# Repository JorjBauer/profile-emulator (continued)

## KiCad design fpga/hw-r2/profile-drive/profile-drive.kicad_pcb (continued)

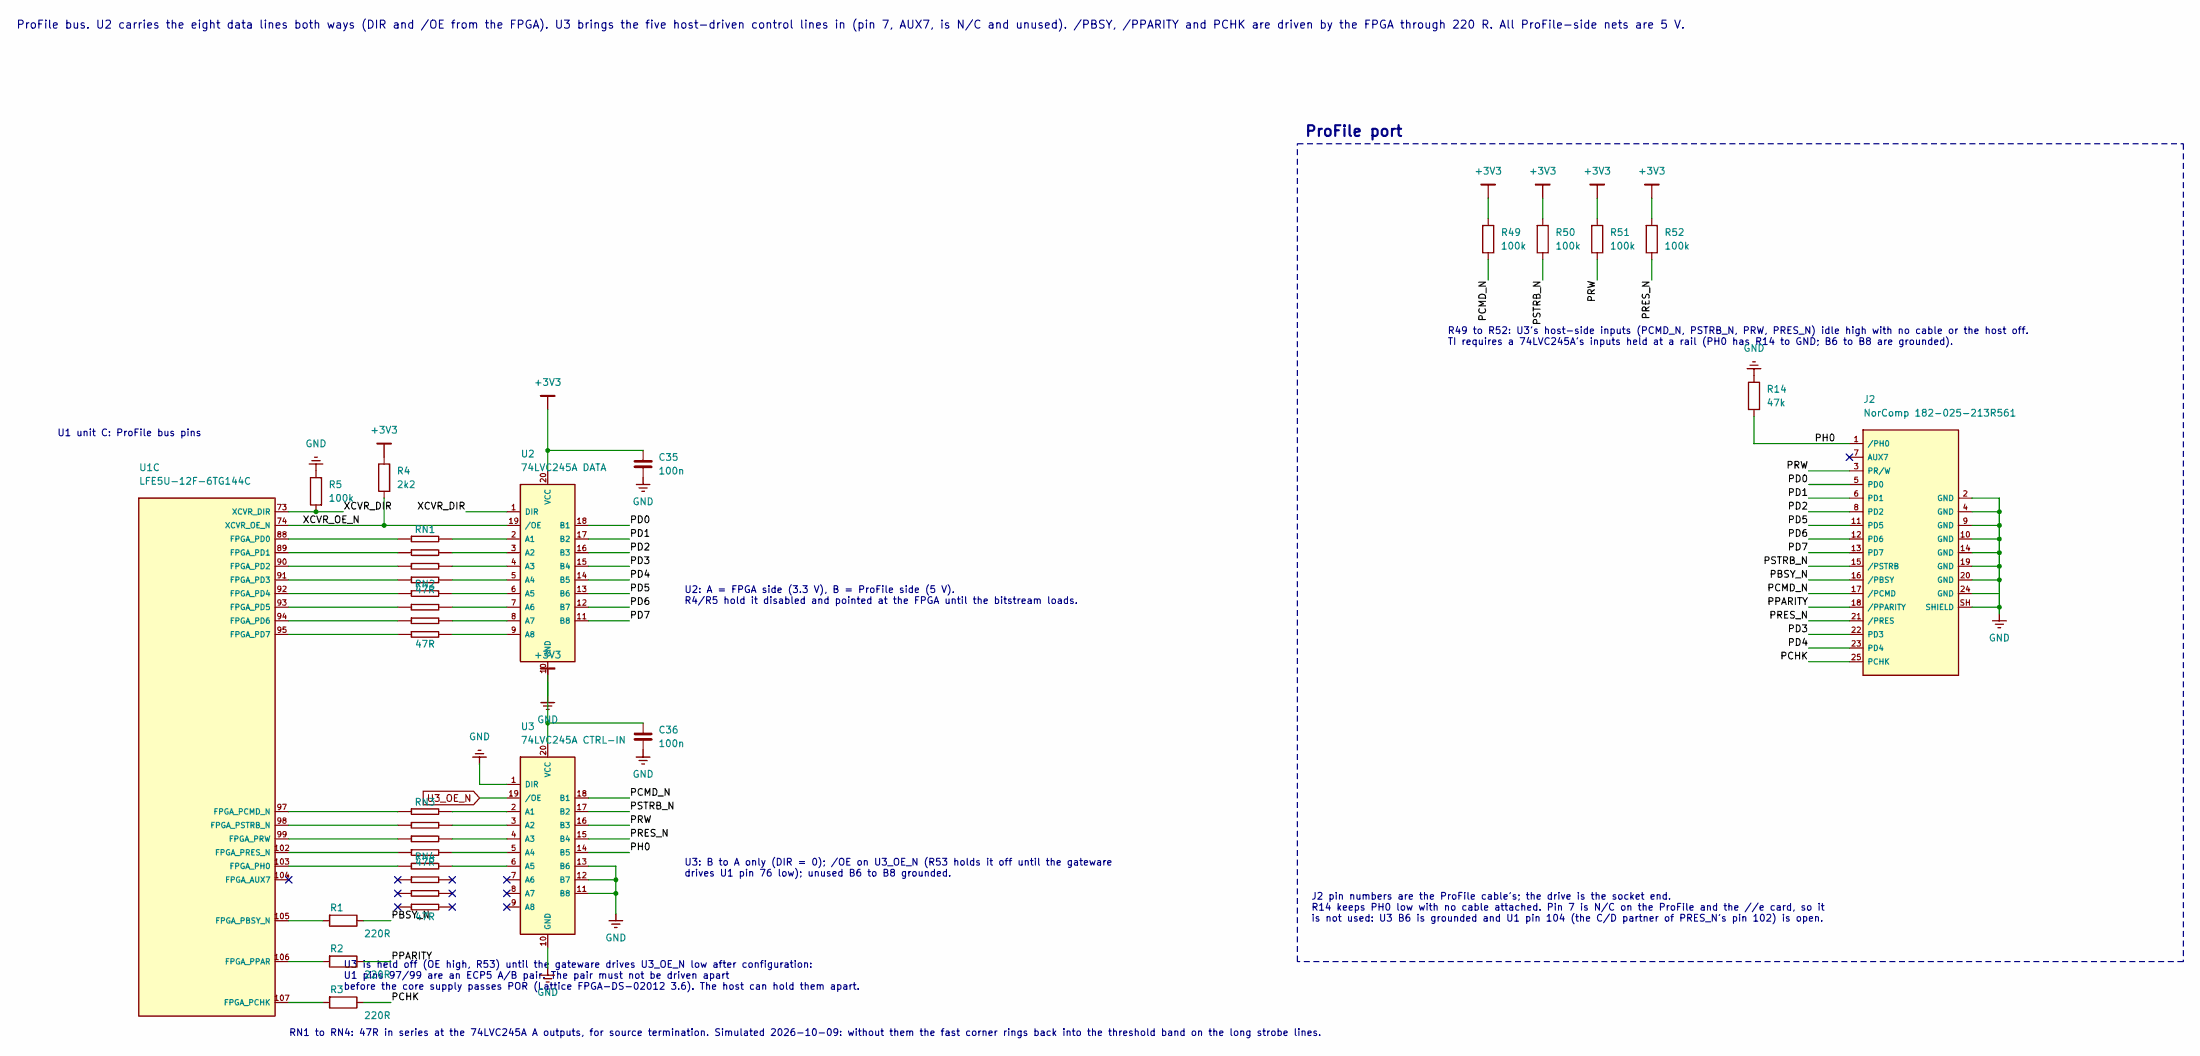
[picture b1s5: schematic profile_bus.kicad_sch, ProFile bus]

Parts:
C35, C36: 100n; C_0603_1608Metric; MPN Samsung CL10B104KO8NNNC; LCSC C66501
J2: NorComp 182-025-213R561; DSUB-25_Female_Horizontal_NorComp_182-025-213R561; MPN NorComp 182-025-213R561; LCSC C17257261
R1, R2, R3: 220R; R_0603_1608Metric; MPN Yageo RC0603FR-07220RL; LCSC C107696
R4: 2k2; R_0603_1608Metric; MPN Yageo RC0603FR-072K2L; LCSC C114662
R5, R49, R50, R51, R52: 100k; R_0603_1608Metric; MPN Yageo RC0603FR-07100KL; LCSC C14675
R14: 47k; R_0603_1608Metric; MPN Yageo RC0603FR-0747KL; LCSC C105579
RN1, RN2, RN3, RN4: 47R; R_Array_Convex_4x0603_Yageo_YC164; MPN Yageo YC164-FR-0747RL; LCSC C606217
U1: LFE5U-12F-6TG144C; TQFP-144_20x20mm_P0.5mm; MPN Lattice LFE5U-12F-6TG144C; LCSC C19979181
U2: 74LVC245A DATA; TSSOP-20_4.4x6.5mm_P0.65mm; MPN TI SN74LVC245APWR; LCSC C7848
U3: 74LVC245A CTRL-IN; TSSOP-20_4.4x6.5mm_P0.65mm; MPN TI SN74LVC245APWR; LCSC C7848

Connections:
/ProFile bus/PBSY_N: J2.16 (/PBSY), R1.2
/ProFile bus/PCHK: J2.25 (PCHK), R3.2
/ProFile bus/PCMD_N: J2.17 (/PCMD), R49.2, U3.18 (B1)
/ProFile bus/PD0: J2.5 (PD0), U2.18 (B1)
/ProFile bus/PD1: J2.6 (PD1), U2.17 (B2)
/ProFile bus/PD2: J2.8 (PD2), U2.16 (B3)
/ProFile bus/PD3: J2.22 (PD3), U2.15 (B4)
/ProFile bus/PD4: J2.23 (PD4), U2.14 (B5)
/ProFile bus/PD5: J2.11 (PD5), U2.13 (B6)
/ProFile bus/PD6: J2.12 (PD6), U2.12 (B7)
/ProFile bus/PD7: J2.13 (PD7), U2.11 (B8)
/ProFile bus/PH0: J2.1 (/PH0), R14.1, U3.14 (B5)
/ProFile bus/PPARITY: J2.18 (/PPARITY), R2.2
/ProFile bus/PRES_N: J2.21 (/PRES), R52.2, U3.15 (B4)
/ProFile bus/PRW: J2.3 (PR/W), R51.2, U3.16 (B3)
/ProFile bus/PSTRB_N: J2.15 (/PSTRB), R50.2, U3.17 (B2)
/ProFile bus/XCVR_DIR: R5.1, U1.73 (XCVR_DIR), U2.1 (DIR)
/ProFile bus/XCVR_OE_N: R4.1, U1.74 (XCVR_OE_N), U2.19 (/OE)
unnamed: R1.1, U1.105 (FPGA_PBSY_N)
unnamed: R3.1, U1.107 (FPGA_PCHK)
unnamed: RN3.1, U1.97 (FPGA_PCMD_N)
unnamed: RN1.1, U1.88 (FPGA_PD0)
unnamed: RN1.2, U1.89 (FPGA_PD1)
unnamed: RN1.3, U1.90 (FPGA_PD2)
unnamed: RN1.4, U1.91 (FPGA_PD3)
unnamed: RN2.1, U1.92 (FPGA_PD4)
unnamed: RN2.2, U1.93 (FPGA_PD5)
unnamed: RN2.3, U1.94 (FPGA_PD6)
unnamed: RN2.4, U1.95 (FPGA_PD7)
unnamed: RN4.1, U1.103 (FPGA_PH0)
unnamed: R2.1, U1.106 (FPGA_PPAR)
unnamed: RN3.4, U1.102 (FPGA_PRES_N)
unnamed: RN3.3, U1.99 (FPGA_PRW)
unnamed: RN3.2, U1.98 (FPGA_PSTRB_N)
unnamed: RN1.8, U2.2 (A1)
unnamed: RN1.7, U2.3 (A2)
unnamed: RN1.6, U2.4 (A3)
unnamed: RN1.5, U2.5 (A4)
unnamed: RN2.8, U2.6 (A5)
unnamed: RN2.7, U2.7 (A6)
unnamed: RN2.6, U2.8 (A7)
unnamed: RN2.5, U2.9 (A8)
unnamed: RN3.8, U3.2 (A1)
unnamed: RN3.7, U3.3 (A2)
unnamed: RN3.6, U3.4 (A3)
unnamed: RN3.5, U3.5 (A4)
unnamed: RN4.8, U3.6 (A5)
U3_OE_N: U3.19 (/OE); also elsewhere on the board

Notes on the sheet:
ProFile bus. U2 carries the eight data lines both ways (DIR and /OE from the FPGA). U3 brings the five host-driven control lines in (pin 7, AUX7, is N/C and unused). /PBSY, /PPARITY and PCHK are driven by the FPGA through 220 R. All ProFile-side nets are 5 V.
U1 unit C: ProFile bus pins
U2: A = FPGA side (3.3 V), B = ProFile side (5 V). R4/R5 hold it disabled and pointed at the FPGA until the bitstream loads.
U3: B to A only (DIR = 0); /OE on U3_OE_N (R53 holds it off until the gateware drives U1 pin 76 low); unused B6 to B8 grounded.
ProFile port
J2 pin numbers are the ProFile cable's; the drive is the socket end. R14 keeps PH0 low with no cable attached. Pin 7 is N/C on the ProFile and the //e card, so it is not used: U3 B6 is grounded and U1 pin 104 (the C/D partner of PRES_N's pin 102) is open.
RN1 to RN4: 47R in series at the 74LVC245A A outputs, for source termination. Simulated 2026-10-09: without them the fast corner rings back into the threshold band on the long strobe lines.
R49 to R52: U3's host-side inputs (PCMD_N, PSTRB_N, PRW, PRES_N) idle high with no cable or the host off. TI requires a 74LVC245A's inputs held at a rail (PH0 has R14 to GND; B6 to B8 are grounded).
U3 is held off (OE high, R53) until the gateware drives U3_OE_N low after configuration: U1 pins 97/99 are an ECP5 A/B pair. The pair must not be driven apart before the core supply passes POR (Lattice FPGA-DS-02012 3.6). The host can hold them apart.

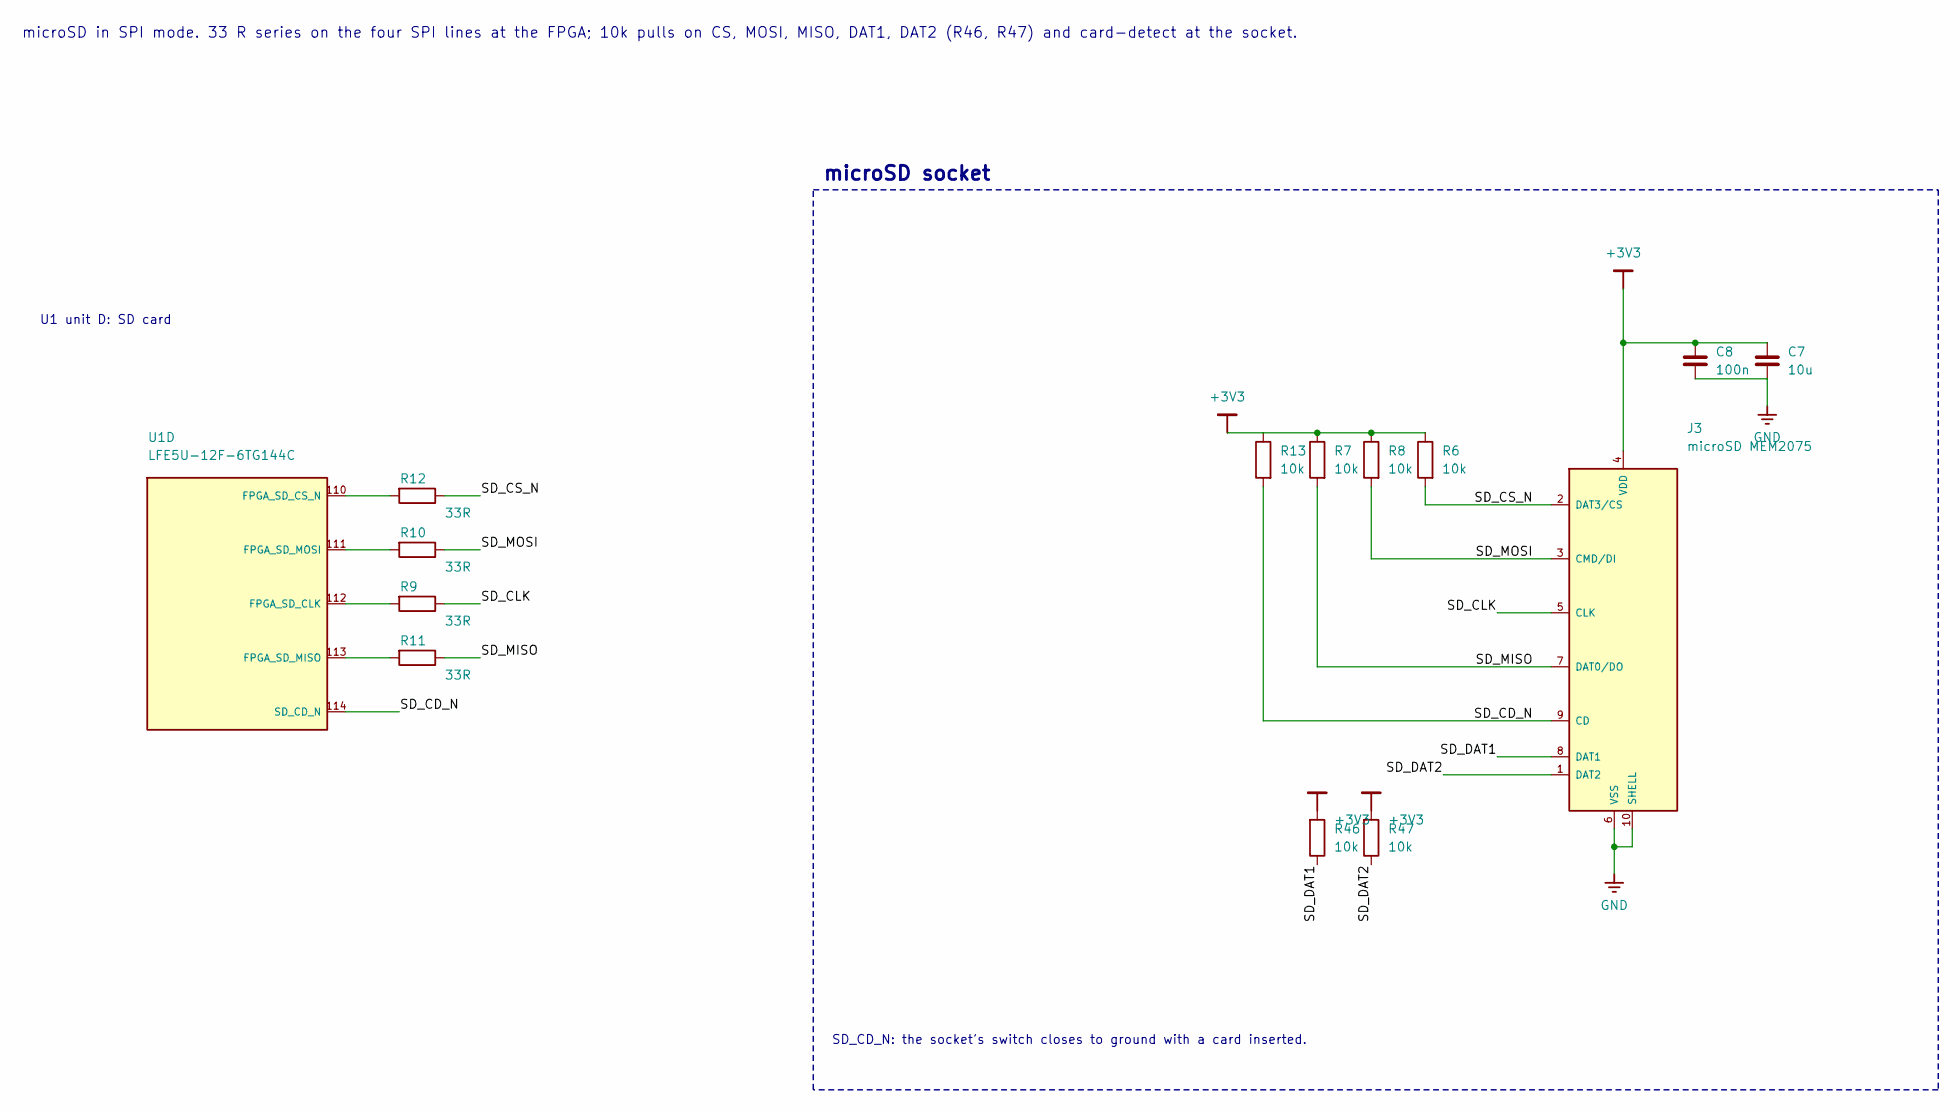
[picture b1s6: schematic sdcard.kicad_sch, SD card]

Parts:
C7: 10u; C_0603_1608Metric; MPN Murata GRM188R61E106MA73D; LCSC C91606
C8: 100n; C_0603_1608Metric; MPN Samsung CL10B104KO8NNNC; LCSC C66501
J3: microSD MEM2075; microSD_GCT_MEM2075; MPN GCT MEM2075-00-140-01-A; LCSC C3029735
R6, R7, R8, R13, R46, R47: 10k; R_0603_1608Metric; MPN Yageo RC0603FR-0710KL; LCSC C98220
R9, R10, R11, R12: 33R; R_0603_1608Metric; MPN Yageo RC0603FR-0733RL; LCSC C108661
U1: LFE5U-12F-6TG144C; TQFP-144_20x20mm_P0.5mm; MPN Lattice LFE5U-12F-6TG144C; LCSC C19979181

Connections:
/SD card/SD_CD_N: J3.9 (CD), R13.1, U1.114 (SD_CD_N)
/SD card/SD_CLK: J3.5 (CLK), R9.2
/SD card/SD_CS_N: J3.2 (DAT3/CS), R6.1, R12.2
/SD card/SD_DAT1: J3.8 (DAT1), R46.2
/SD card/SD_DAT2: J3.1 (DAT2), R47.2
/SD card/SD_MISO: J3.7 (DAT0/DO), R7.1, R11.2
/SD card/SD_MOSI: J3.3 (CMD/DI), R8.1, R10.2
unnamed: R9.1, U1.112 (FPGA_SD_CLK)
unnamed: R12.1, U1.110 (FPGA_SD_CS_N)
unnamed: R11.1, U1.113 (FPGA_SD_MISO)
unnamed: R10.1, U1.111 (FPGA_SD_MOSI)

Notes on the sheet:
microSD in SPI mode. 33 R series on the four SPI lines at the FPGA; 10k pulls on CS, MOSI, MISO, DAT1, DAT2 (R46, R47) and card-detect at the socket.
U1 unit D: SD card
microSD socket
SD_CD_N: the socket's switch closes to ground with a card inserted.

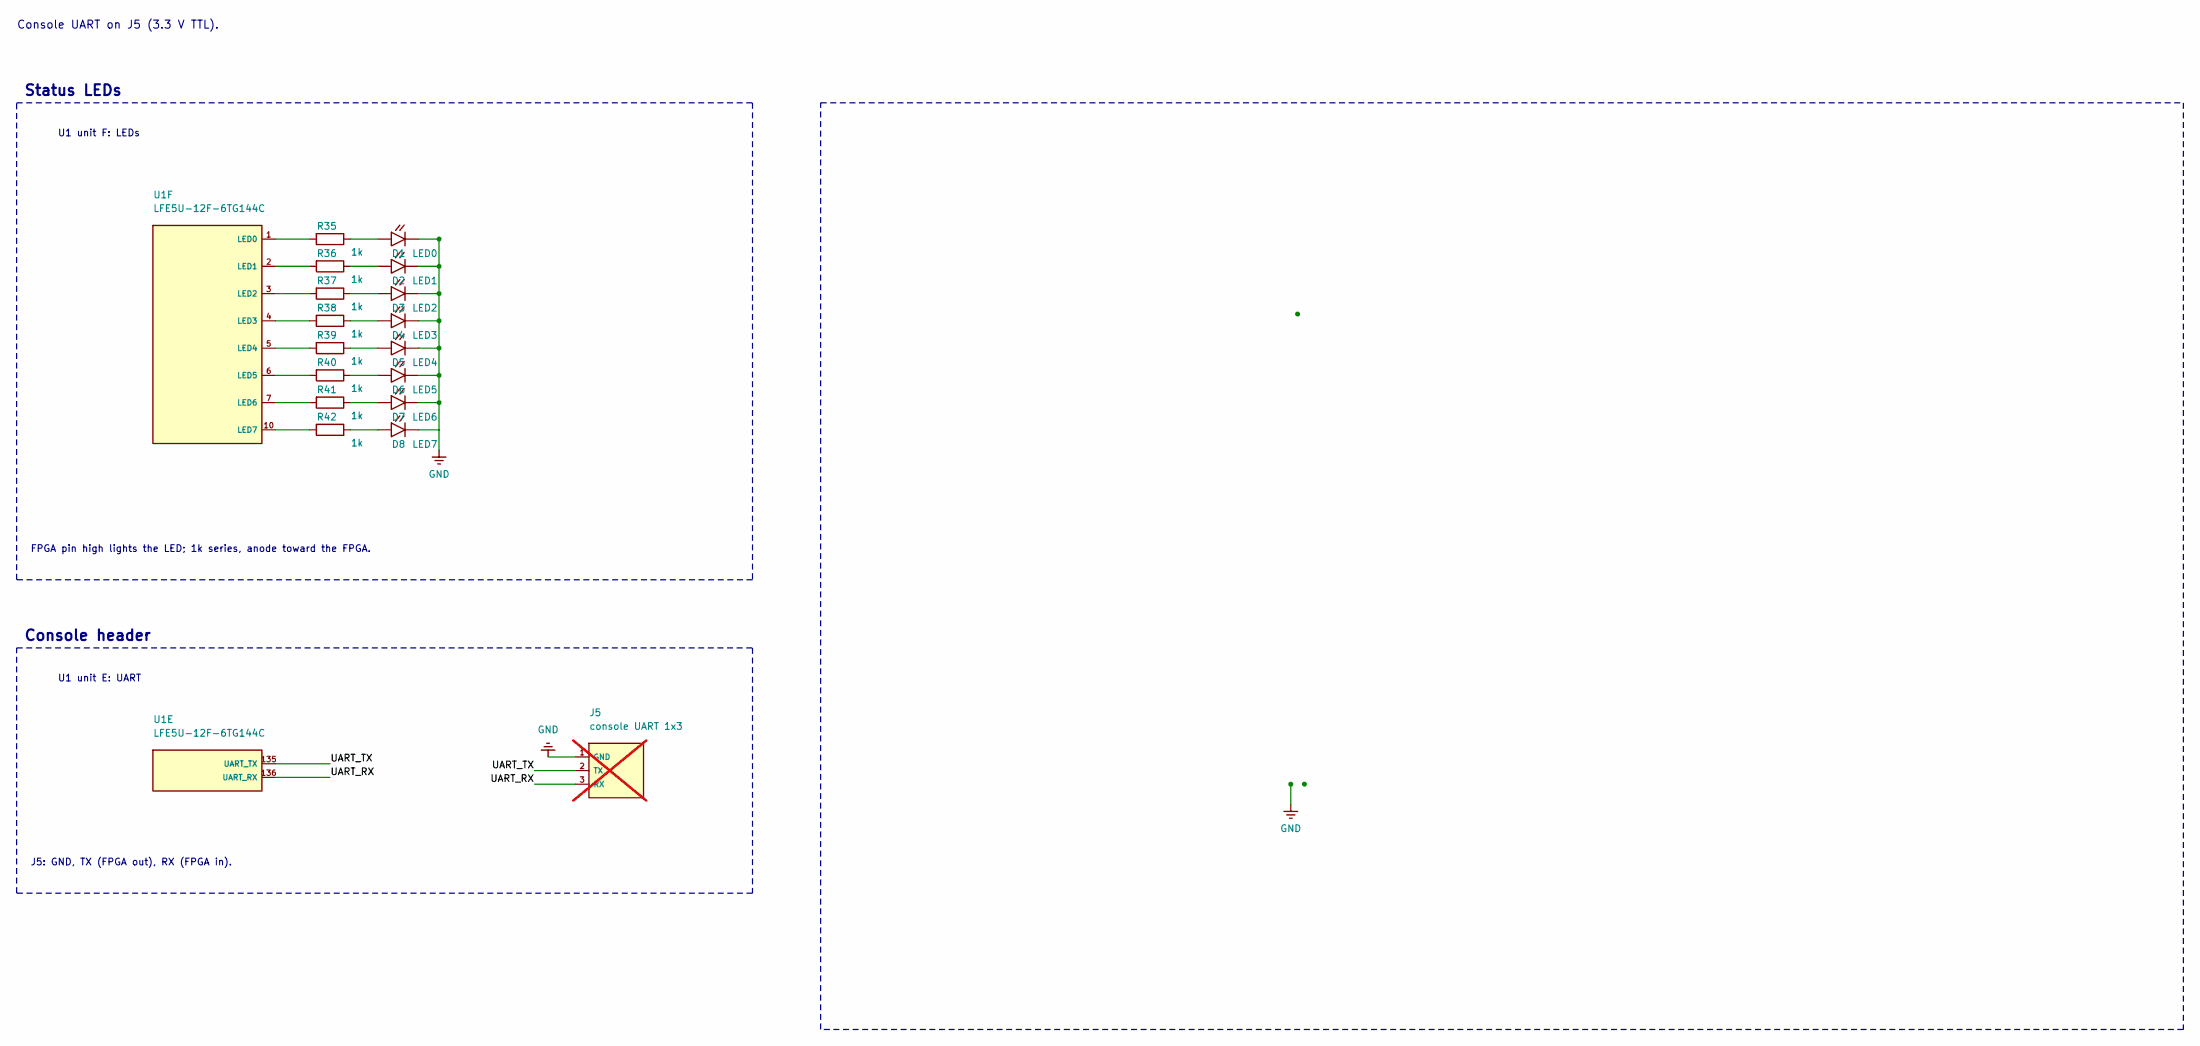
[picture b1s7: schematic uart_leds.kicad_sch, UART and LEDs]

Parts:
D1: LED0; LED_0603_1608Metric; LCSC C2286
D2: LED1; LED_0603_1608Metric; LCSC C2286
D3: LED2; LED_0603_1608Metric; LCSC C2286
D4: LED3; LED_0603_1608Metric; LCSC C2286
D5: LED4; LED_0603_1608Metric; LCSC C2286
D6: LED5; LED_0603_1608Metric; LCSC C2286
D7: LED6; LED_0603_1608Metric; LCSC C2286
D8: LED7; LED_0603_1608Metric; LCSC C2286
J5: console UART 1x3; PinHeader_1x03_P2.54mm_Vertical; not fitted
R35, R36, R37, R38, R39, R40, R41, R42: 1k; R_0603_1608Metric; MPN Yageo RC0603FR-071KL; LCSC C22548
U1: LFE5U-12F-6TG144C; TQFP-144_20x20mm_P0.5mm; MPN Lattice LFE5U-12F-6TG144C; LCSC C19979181

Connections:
/UART and LEDs/UART_RX: J5.3 (RX), U1.136 (UART_RX)
/UART and LEDs/UART_TX: J5.2 (TX), U1.135 (UART_TX)
unnamed: D1.2 (A), R35.2
unnamed: D2.2 (A), R36.2
unnamed: D3.2 (A), R37.2
unnamed: D4.2 (A), R38.2
unnamed: D5.2 (A), R39.2
unnamed: D6.2 (A), R40.2
unnamed: D7.2 (A), R41.2
unnamed: D8.2 (A), R42.2
unnamed: R35.1, U1.1 (LED0)
unnamed: R36.1, U1.2 (LED1)
unnamed: R37.1, U1.3 (LED2)
unnamed: R38.1, U1.4 (LED3)
unnamed: R39.1, U1.5 (LED4)
unnamed: R40.1, U1.6 (LED5)
unnamed: R41.1, U1.7 (LED6)
unnamed: R42.1, U1.10 (LED7)

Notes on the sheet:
Console UART on J5 (3.3 V TTL).
Status LEDs
U1 unit F: LEDs
FPGA pin high lights the LED; 1k series, anode toward the FPGA.
Console header
U1 unit E: UART
J5: GND, TX (FPGA out), RX (FPGA in).

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
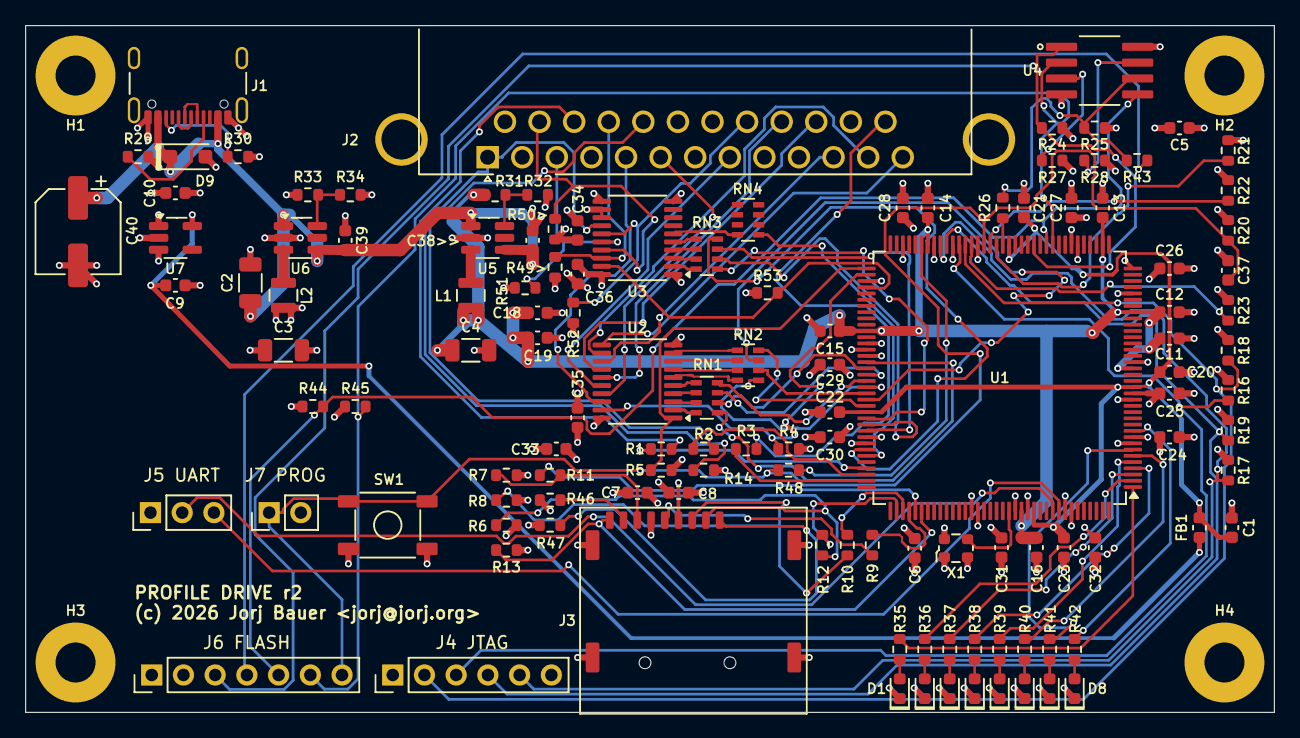
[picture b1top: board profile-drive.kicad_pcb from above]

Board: 4 copper layers, 100.0 x 55.0 mm, 127 parts (0 on the bottom side), 109 nets.

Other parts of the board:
H1, H2, H3, H4: M3; MountingHole_3.2mm_M3_Pad

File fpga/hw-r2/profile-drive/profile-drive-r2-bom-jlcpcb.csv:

"Comment","Designator","Footprint","Manufacturer Part","LCSC Part #"
"10u","C1,C7,C9,C18,C19,C33,C34,C38,C39","C_0603_1608Metric","Murata GRM188R61E106MA73D","C91606"
"22u","C2,C3,C4","C_1206_3216Metric","Samsung CL31A226KAHNNNE","C12891"
"100n","C5,C6,C8,C11,C12,C13,C14,C15,C16,C20,C21,C22,C23,C24,C25,C26,C27,C28,C29,C30,C31,C32,C35,C36","C_0603_1608Metric","Samsung CL10B104KO8NNNC","C66501"
"1u","C10,C37","C_0603_1608Metric","Samsung CL10B105KA8NNNC","C29936"
"100u","C40","CP_Elec_6.3x5.8","Panasonic EEE-FK1C101P","C128532"
"LED red 0603","D1,D2,D3,D4,D5,D6,D7,D8","LED_0603_1608Metric","Hubei KENTO KT-0603R","C2286"
"SMF5.0A","D9","D_SOD-123F","Littelfuse SMF5.0A","C151296"
"120R@100M","FB1","L_0603_1608Metric","Murata BLM18PG121SN1D","C14709"
"USB-C 16p","J1","USB_C_Receptacle_GCT_USB4105-xx-A_16P_TopMnt_Horizontal","GCT USB4105-GF-A","C3020560"
"NorComp 182-025-213R561","J2","DSUB-25_Female_Horizontal_NorComp_182-025-213R561","NorComp 182-025-213R561","C17257261"
"microSD MEM2075","J3","microSD_GCT_MEM2075","GCT MEM2075-00-140-01-A","C3029735"
"1u0","L1,L2","L_Murata_DFE252012F","Murata DFE252012F-1R0M=P2","C435392"
"220R","R1,R2,R3","R_0603_1608Metric","Yageo RC0603FR-07220RL","C107696"
"2k2","R4,R53","R_0603_1608Metric","Yageo RC0603FR-072K2L","C114662"
"100k","R5,R32,R49,R50,R51,R52","R_0603_1608Metric","Yageo RC0603FR-07100KL","C14675"
"10k","R6,R7,R8,R13,R27,R28,R44,R45,R46,R47","R_0603_1608Metric","Yageo RC0603FR-0710KL","C98220"
"33R","R9,R10,R11,R12","R_0603_1608Metric","Yageo RC0603FR-0733RL","C108661"
"47k","R14","R_0603_1608Metric","Yageo RC0603FR-0747KL","C105579"
"4k7","R16,R17,R18,R19,R20,R21,R22,R23,R24","R_0603_1608Metric","Yageo RC0603FR-074K7L","C99782"
"1k","R25,R35,R36,R37,R38,R39,R40,R41,R42","R_0603_1608Metric","Yageo RC0603FR-071KL","C22548"
"22R","R26","R_0603_1608Metric","Yageo RC0603FR-0722RL","C107701"
"5k1","R29,R30","R_0603_1608Metric","Yageo RC0603FR-075K1L","C105580"
"84.5k","R31","R_0603_1608Metric","Yageo RC0603FR-0784K5L","C326920"
"274k","R33","R_0603_1608Metric","Yageo RC0603FR-07274KL","C482818"
"60k4","R34","R_0603_1608Metric","Yageo RC0603FR-0760K4L","C165742"
"100R","R43,R48","R_0603_1608Metric","Yageo RC0603FR-07100RL","C105588"
"47R","RN1,RN2,RN3,RN4","R_Array_Convex_4x0603_Yageo_YC164","Yageo YC164-FR-0747RL","C606217"
"LFE5U-12F-6TG144C","U1","TQFP-144_20x20mm_P0.5mm","Lattice LFE5U-12F-6TG144C","C19979181"
"74LVC245A","U2,U3","TSSOP-20_4.4x6.5mm_P0.65mm","TI SN74LVC245APWR","C7848"
"W25Q128JVSIQ","U4","SOIC-8_Dual_150-208mil_P1.27mm","Winbond W25Q128JVSIQ","C97521"
"TPS62A01A","U5,U6","SOT-23-6_Handsoldering","TI TPS62A01APDDCR","C41730179"
"TLV73325PDBV 2V5","U7","SOT-23-5_HandSoldering","TI TLV73325PDBVR","C882825"
"25MHz XO 2520 3V3","X1","Oscillator_SMD_ECS_2520MV-xxx-xx-4Pin_2.5x2.0mm","ECS ECS-2520MV-250-BN-TR","C405463"

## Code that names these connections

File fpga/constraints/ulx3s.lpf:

# ULX3S (ECP5, caBGA381) pin constraints, wired to the interface board's J2.
#
# THREE hops, and every one of them is written down rather than remembered:
#
#   1. interface board net -> its J2 pin      ../../HARDWARE.md
#   2. interface J2 pin    -> ULX3S J2 pin    carrier/ULX3S-ADAPTER.md
#   3. ULX3S GP/GN name    -> ECP5 ball       emard ulx3s_v20.lpf
#
# Hop 3 comes from emard's ulx3s_v20.lpf, not typed from memory: a guess that
# lands on a real but wrong ball programs cleanly and the board does nothing.
#
# That file is for board revision v2.0. Several GP/GN balls MOVED between
# revisions (its own comments record E15->C15, C15->E14, D15->B15, B15->D14).
# If this board is not a v2.x, re-extract hop 3 rather than editing it.
#
# Build:
#   yosys -p 'read_verilog <src>; synth_ecp5 -top top -json profile_emu.json'
#   nextpnr-ecp5 --25k --package CABGA381 --json profile_emu.json \
#                --lpf constraints/ulx3s.lpf --textcfg profile_emu.config
#   ecppack profile_emu.config profile_emu.bit
#   openFPGALoader -b ulx3s profile_emu.bit
#
# --25k, not --12k, EVEN ON A BOARD SOLD AS A 12F: the ULX3S 12F carries 25F
# silicon and targeting it as a 25F is standard practice for this board. The
# usable fabric is 24288 LUT4, not 12144.

BLOCK RESETPATHS;
BLOCK ASYNCPATHS;

# --- on-board, not through J2 ----------------------------------------------
# 25 MHz. src/top.v's PLL takes 25 in and puts 50 out, so clk_sys is 50 MHz
# and every CLK_HZ constant in the design (SD dividers, token timeouts, UART
# baud, reporter, verifier) keeps its value.
LOCATE COMP "clk"    SITE "G2";
IOBUF  PORT "clk"    PULLMODE=NONE IO_TYPE=LVCMOS33;

# FIRE1, pulled DOWN, so it reads 0 idle and 1 pressed. top.v wants rst_n, so
# the wrapper inverts it. btn[0] is BTN_PWRn and its sense is documented as
# "inverted logic", which is too ambiguous to build a reset on.
LOCATE COMP "rst_n"  SITE "R1";
IOBUF  PORT "rst_n"  PULLMODE=DOWN IO_TYPE=LVCMOS33;

# FPGA transmits to the FTDI, so the FPGA's TX output is the net called
# ftdi_rxd. Only TX is used.
LOCATE COMP "usb_tx" SITE "L4";
IOBUF  PORT "usb_tx" PULLMODE=UP IO_TYPE=LVCMOS33 DRIVE=4;

# The FTDI's transmit into the FPGA: the bench command channel (uart_rx).
LOCATE COMP "usb_rx" SITE "M1";
IOBUF  PORT "usb_rx" PULLMODE=UP IO_TYPE=LVCMOS33;

LOCATE COMP "led[0]" SITE "B2";
LOCATE COMP "led[1]" SITE "C2";
LOCATE COMP "led[2]" SITE "C1";
LOCATE COMP "led[3]" SITE "D2";
LOCATE COMP "led[4]" SITE "D1";
LOCATE COMP "led[5]" SITE "E2";
LOCATE COMP "led[6]" SITE "E1";
LOCATE COMP "led[7]" SITE "H3";
IOBUF  PORT "led[0]" IO_TYPE=LVCMOS33 DRIVE=4;
IOBUF  PORT "led[1]" IO_TYPE=LVCMOS33 DRIVE=4;
IOBUF  PORT "led[2]" IO_TYPE=LVCMOS33 DRIVE=4;
IOBUF  PORT "led[3]" IO_TYPE=LVCMOS33 DRIVE=4;
IOBUF  PORT "led[4]" IO_TYPE=LVCMOS33 DRIVE=4;
IOBUF  PORT "led[5]" IO_TYPE=LVCMOS33 DRIVE=4;
IOBUF  PORT "led[6]" IO_TYPE=LVCMOS33 DRIVE=4;
IOBUF  PORT "led[7]" IO_TYPE=LVCMOS33 DRIVE=4;

# --- HOW THIS MAP WAS CHOSEN -----------------------------------------------
# The two headers FACE each other, so their numbering runs in opposite
# directions: interface J2.1 sits nearest ULX3S pin 79, and J2.35 nearest pin
# 41. A wire is therefore its shortest when x_ulx3s(p) == x_if(q), which works
# out to p + q = 20.
#
# Every signal whose aligned position exists is placed there, so 22 of the 25
# wires run straight across. Only three cannot, because their aligned position
# lands on a ULX3S power pin: IF J2.18 (PD7), J2.35 (SD_CD) and J2.36 (SD_WP).
# SD_WP is given the long run of the three because it is a mechanical switch
# contact that never toggles, and HONOR_WP is 0.
#
# Columns: ECP5 ball / ULX3S signal / ULX3S J2 board pin / interface J2 pin.

# --- GP row: the interface board's even pins -------------------------------
# Bit order is not free: PD7 goes to DB-25 pin 13 and PD0 to DB-25 pin 5. See
# the data-bus mapping table in ../../HARDWARE.md. The byte reads high-to-low
# across the connector here, which is the facing orientation, not a mistake.
LOCATE COMP "pd[0]"  SITE "D13";  # GP27  J2.76  IF J2.4   DB-25 5
LOCATE COMP "pd[1]"  SITE "B13";  # GP26  J2.74  IF J2.6   DB-25 6
LOCATE COMP "pd[2]"  SITE "D14";  # GP25  J2.72  IF J2.8   DB-25 8
LOCATE COMP "pd[3]"  SITE "C16";  # GP24  J2.70  IF J2.10  DB-25 22
LOCATE COMP "pd[4]"  SITE "B17";  # GP23  J2.68  IF J2.12  DB-25 23
LOCATE COMP "pd[5]"  SITE "B15";  # GP22  J2.66  IF J2.14  DB-25 11
LOCATE COMP "pd[6]"  SITE "C18";  # GP21  J2.64  IF J2.16  DB-25 12
LOCATE COMP "pd[7]"  SITE "C15";  # GN22  J2.65  IF J2.18  DB-25 13  <- see note
IOBUF  PORT "pd[0]"  IO_TYPE=LVCMOS33 DRIVE=8;
IOBUF  PORT "pd[1]"  IO_TYPE=LVCMOS33 DRIVE=8;
IOBUF  PORT "pd[2]"  IO_TYPE=LVCMOS33 DRIVE=8;
IOBUF  PORT "pd[3]"  IO_TYPE=LVCMOS33 DRIVE=8;
IOBUF  PORT "pd[4]"  IO_TYPE=LVCMOS33 DRIVE=8;
IOBUF  PORT "pd[5]"  IO_TYPE=LVCMOS33 DRIVE=8;
IOBUF  PORT "pd[6]"  IO_TYPE=LVCMOS33 DRIVE=8;
IOBUF  PORT "pd[7]"  IO_TYPE=LVCMOS33 DRIVE=8;
# PD7 is the only data bit on the GN row. Its aligned position (p=11) is a
# ULX3S power pin, and the GP row is full at 14 of 14, so it has nowhere else
# to be. Seven bits sit in BANK1 and PD6 in BANK2/BANK3; at ProFile byte rates
# the bank difference is far below anything that matters.

# Host-driven lines, through U2.
LOCATE COMP "pcmd_n"   SITE "D18";  # GP20  J2.58  IF J2.22  DB-25 17
LOCATE COMP "pstrb_n"  SITE "F17";  # GP19  J2.56  IF J2.24  DB-25 15
LOCATE COMP "prw"      SITE "H18";  # GP18  J2.54  IF J2.26  DB-25 3
LOCATE COMP "pres_n"   SITE "L16";  # GP17  J2.52  IF J2.28  DB-25 21
IOBUF  PORT "pcmd_n"   PULLMODE=NONE IO_TYPE=LVCMOS33;
IOBUF  PORT "pstrb_n"  PULLMODE=NONE IO_TYPE=LVCMOS33;
IOBUF  PORT "prw"      PULLMODE=NONE IO_TYPE=LVCMOS33;
IOBUF  PORT "pres_n"   PULLMODE=NONE IO_TYPE=LVCMOS33;

# Shared with SmartPort, host-driven inputs through U2.
LOCATE COMP "ph0"      SITE "N16";  # GP16  J2.50  IF J2.30  DB-25 1 = /PH0
LOCATE COMP "aux7"     SITE "N17";  # GP15  J2.48  IF J2.32  DB-25 7 = SmartPort /ENABLE1
IOBUF  PORT "ph0"      PULLMODE=NONE IO_TYPE=LVCMOS33;
IOBUF  PORT "aux7"     PULLMODE=NONE IO_TYPE=LVCMOS33;

# The only microSD line on the GP row, and it is aligned: IF J2.34 faces GP14.
LOCATE COMP "sd_cs_n"  SITE "U18";  # GP14  J2.46  IF J2.34
IOBUF  PORT "sd_cs_n"  IO_TYPE=LVCMOS33 DRIVE=8;

# --- GN row: the interface board's odd pins, plus PD7 and SD_WP ------------
LOCATE COMP "xcvr_dir"   SITE "E13";  # GN27  J2.75  IF J2.3
LOCATE COMP "xcvr_oe_n"  SITE "C13";  # GN26  J2.73  IF J2.5
IOBUF  PORT "xcvr_dir"   IO_TYPE=LVCMOS33 DRIVE=8;
IOBUF  PORT "xcvr_oe_n"  IO_TYPE=LVCMOS33 DRIVE=8;

LOCATE COMP "sd_clk"   SITE "E17";  # GN20  J2.57  IF J2.21
LOCATE COMP "pbsy_n"   SITE "G18";  # GN19  J2.55  IF J2.23  DB-25 16
LOCATE COMP "sd_mosi"  SITE "H17";  # GN18  J2.53  IF J2.25   socket DI
LOCATE COMP "pparity"  SITE "L17";  # GN17  J2.51  IF J2.27  DB-25 18, both directions
LOCATE COMP "sd_miso"  SITE "M17";  # GN16  J2.49  IF J2.29   socket DO
LOCATE COMP "pchk"     SITE "P16";  # GN15  J2.47  IF J2.31  DB-25 25, grounded = present
LOCATE COMP "sd_cd_n"  SITE "U17";  # GN14  J2.45  IF J2.35   card detect, one position over
LOCATE COMP "sd_wp_n"  SITE "D17";  # GN21  J2.63  IF J2.36   the long wire; see the note above
IOBUF  PORT "sd_clk"   IO_TYPE=LVCMOS33 DRIVE=8;
IOBUF  PORT "pbsy_n"   IO_TYPE=LVCMOS33 DRIVE=8;
IOBUF  PORT "sd_mosi"  IO_TYPE=LVCMOS33 DRIVE=8;
IOBUF  PORT "pparity"  IO_TYPE=LVCMOS33 DRIVE=8;
IOBUF  PORT "sd_miso"  PULLMODE=UP IO_TYPE=LVCMOS33;
IOBUF  PORT "pchk"     IO_TYPE=LVCMOS33 DRIVE=8;
IOBUF  PORT "sd_cd_n"  PULLMODE=UP IO_TYPE=LVCMOS33;
IOBUF  PORT "sd_wp_n"  PULLMODE=UP IO_TYPE=LVCMOS33;

# usb_tx_alt exists only for the iCE40 reference arm; the ECP5 build drives it
# constant-high. Parked on spare GN23 so this file stays strict about ports
# that appear by accident.
LOCATE COMP "usb_tx_alt" SITE "C17";  # GN23  J2.67  spare
IOBUF  PORT "usb_tx_alt" IO_TYPE=LVCMOS33 DRIVE=4;

# The configuration flash's data pins, as ULX3S wires them. Only r2 builds the
# SD firmware update in; here /CS just sits high and MOSI low, so the flash
# stays deselected.
LOCATE COMP "flash_csn"  SITE "R2";
IOBUF  PORT "flash_csn"  IO_TYPE=LVCMOS33;
LOCATE COMP "flash_mosi" SITE "W2";
IOBUF  PORT "flash_mosi" IO_TYPE=LVCMOS33;
LOCATE COMP "flash_miso" SITE "V2";
IOBUF  PORT "flash_miso" IO_TYPE=LVCMOS33;

# fpga_reboot is r2's line to PROGRAMN. The ULX3S build never drives it, so
# it's an input here, parked on spare GN24.
LOCATE COMP "fpga_reboot" SITE "D16";  # GN24  J2.69  spare
IOBUF  PORT "fpga_reboot" PULLMODE=NONE IO_TYPE=LVCMOS33;

# --- spare GN pins ----------------------------------------------------------
#   GN23  C17   J2.67   <- taken by usb_tx_alt above (idle-high, never toggles)
#   GN24  D16   J2.69   <- taken by fpga_reboot above (never driven)
#   GN25  E14   J2.71
#
# NOT constrained here: leaving them out means nextpnr will refuse a design
# that starts using one by accident, which is the behavior wanted.

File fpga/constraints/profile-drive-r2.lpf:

# ProFile drive replacement r2, LFE5U-12F TQFP144.
# Pin assignments follow hw-r2/profile-drive/profile-drive.kicad_pcb.
# The top module is top_r2 (src/top_r2.v), which wraps top and adds the three
# pins the ULX3S build does not have: u3_oe_n, fpga_reboot, and the gated
# xcvr_oe_n. Build with --25k, then ecppack --idcode 0x21111043.
# TQFP144 sites are plain pin numbers.

BLOCK RESETPATHS;
BLOCK ASYNCPATHS;

# AUX7 was dropped on r2 and pin 104 is open; pull it up so it reads
# deasserted (SmartPort /ENABLE1 is active low).
LOCATE COMP "aux7"  SITE "104";
IOBUF  PORT "aux7"  PULLMODE=UP IO_TYPE=LVCMOS33;
LOCATE COMP "clk"  SITE "128";
IOBUF  PORT "clk"  IO_TYPE=LVCMOS33;
LOCATE COMP "led[0]"  SITE "1";
IOBUF  PORT "led[0]"  IO_TYPE=LVCMOS33;
LOCATE COMP "led[1]"  SITE "2";
IOBUF  PORT "led[1]"  IO_TYPE=LVCMOS33;
LOCATE COMP "led[2]"  SITE "3";
IOBUF  PORT "led[2]"  IO_TYPE=LVCMOS33;
LOCATE COMP "led[3]"  SITE "4";
IOBUF  PORT "led[3]"  IO_TYPE=LVCMOS33;
LOCATE COMP "led[4]"  SITE "5";
IOBUF  PORT "led[4]"  IO_TYPE=LVCMOS33;
LOCATE COMP "led[5]"  SITE "6";
IOBUF  PORT "led[5]"  IO_TYPE=LVCMOS33;
LOCATE COMP "led[6]"  SITE "7";
IOBUF  PORT "led[6]"  IO_TYPE=LVCMOS33;
LOCATE COMP "led[7]"  SITE "10";
IOBUF  PORT "led[7]"  IO_TYPE=LVCMOS33;
LOCATE COMP "pbsy_n"  SITE "105";
IOBUF  PORT "pbsy_n"  IO_TYPE=LVCMOS33;
LOCATE COMP "pchk"  SITE "107";
IOBUF  PORT "pchk"  IO_TYPE=LVCMOS33;
LOCATE COMP "pcmd_n"  SITE "97";
IOBUF  PORT "pcmd_n"  IO_TYPE=LVCMOS33;
LOCATE COMP "pd[0]"  SITE "88";
IOBUF  PORT "pd[0]"  IO_TYPE=LVCMOS33;
LOCATE COMP "pd[1]"  SITE "89";
IOBUF  PORT "pd[1]"  IO_TYPE=LVCMOS33;
LOCATE COMP "pd[2]"  SITE "90";
IOBUF  PORT "pd[2]"  IO_TYPE=LVCMOS33;
LOCATE COMP "pd[3]"  SITE "91";
IOBUF  PORT "pd[3]"  IO_TYPE=LVCMOS33;
LOCATE COMP "pd[4]"  SITE "92";
IOBUF  PORT "pd[4]"  IO_TYPE=LVCMOS33;
LOCATE COMP "pd[5]"  SITE "93";
IOBUF  PORT "pd[5]"  IO_TYPE=LVCMOS33;
LOCATE COMP "pd[6]"  SITE "94";
IOBUF  PORT "pd[6]"  IO_TYPE=LVCMOS33;
LOCATE COMP "pd[7]"  SITE "95";
IOBUF  PORT "pd[7]"  IO_TYPE=LVCMOS33;
LOCATE COMP "ph0"  SITE "103";
IOBUF  PORT "ph0"  IO_TYPE=LVCMOS33;
LOCATE COMP "pparity"  SITE "106";
IOBUF  PORT "pparity"  IO_TYPE=LVCMOS33;
LOCATE COMP "pres_n"  SITE "102";
IOBUF  PORT "pres_n"  IO_TYPE=LVCMOS33;
LOCATE COMP "prw"  SITE "99";
IOBUF  PORT "prw"  IO_TYPE=LVCMOS33;
LOCATE COMP "pstrb_n"  SITE "98";
IOBUF  PORT "pstrb_n"  IO_TYPE=LVCMOS33;
LOCATE COMP "sd_cd_n"  SITE "114";
IOBUF  PORT "sd_cd_n"  IO_TYPE=LVCMOS33;
LOCATE COMP "sd_clk"  SITE "112";
IOBUF  PORT "sd_clk"  IO_TYPE=LVCMOS33;
LOCATE COMP "sd_cs_n"  SITE "110";
IOBUF  PORT "sd_cs_n"  IO_TYPE=LVCMOS33;
LOCATE COMP "sd_miso"  SITE "113";
IOBUF  PORT "sd_miso"  IO_TYPE=LVCMOS33;
LOCATE COMP "sd_mosi"  SITE "111";
IOBUF  PORT "sd_mosi"  IO_TYPE=LVCMOS33;
LOCATE COMP "usb_tx"  SITE "135";
IOBUF  PORT "usb_tx"  IO_TYPE=LVCMOS33;
LOCATE COMP "xcvr_dir"  SITE "73";
IOBUF  PORT "xcvr_dir"  IO_TYPE=LVCMOS33;
LOCATE COMP "xcvr_oe_n"  SITE "74";
IOBUF  PORT "xcvr_oe_n"  IO_TYPE=LVCMOS33;

# top.v ports with no role on this board, parked on unrouted pins
# (the same trick as usb_tx_alt on the ULX3S).
LOCATE COMP "rst_n"      SITE "133";
IOBUF  PORT "rst_n"      PULLMODE=UP IO_TYPE=LVCMOS33;
LOCATE COMP "usb_tx_alt" SITE "134";
IOBUF  PORT "usb_tx_alt" IO_TYPE=LVCMOS33;
# sd_wp_n: microSD has no write-protect switch; internal pullup
# reads permanently not-protected (HONOR_WP is 0 in RTL anyway).
LOCATE COMP "sd_wp_n"    SITE "115";
IOBUF  PORT "sd_wp_n"    PULLMODE=UP IO_TYPE=LVCMOS33;

# usb_rx: J5 pin 3, UART_RX. It floats with no adapter on J5.
LOCATE COMP "usb_rx"     SITE "136";
IOBUF  PORT "usb_rx"     PULLMODE=UP IO_TYPE=LVCMOS33;

# r2 only, driven by top_r2.v.
# U3's /OE: R53 holds it high until we are configured, then we drive it low.
LOCATE COMP "u3_oe_n"     SITE "76";
IOBUF  PORT "u3_oe_n"     IO_TYPE=LVCMOS33;
# To PROGRAMN through R48. Low reboots the part; it must never go high. The
# SD firmware update pulls it low through an explicit pad, open drain, after
# it has written the flash; otherwise it's released (see src/top.v).
LOCATE COMP "fpga_reboot" SITE "67";
IOBUF  PORT "fpga_reboot" PULLMODE=NONE IO_TYPE=LVCMOS33;

# The configuration flash (U4) once we're running, for the SD update. Its
# clock is the configuration clock, reached through USRMCLK, so it has no
# entry here. /WP and /HOLD have their own pull-ups on the board.
LOCATE COMP "flash_csn"  SITE "49";
IOBUF  PORT "flash_csn"  IO_TYPE=LVCMOS33;
LOCATE COMP "flash_mosi" SITE "47";
IOBUF  PORT "flash_mosi" IO_TYPE=LVCMOS33;
LOCATE COMP "flash_miso" SITE "46";
IOBUF  PORT "flash_miso" IO_TYPE=LVCMOS33;

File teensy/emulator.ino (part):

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#define PSTRBIN 28  // /PSTRB host strobe  (active low, buffered input)
#define PRWIN   27  // PR/-W  host read/write; ALSO the hardware data-'245 DIR
#define PBSYOUT 25  // /PBSY  drive busy   (active low, DIRECT output)
#define PPAROUT 26  // /PPARITY drive parity (active low, DIRECT output)
#define OE      11  // /OE for both '245s  (active low)

// ---- Media ---------------------------------------------------------------
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  if (!out.open(dst, O_WRONLY | O_CREAT | O_TRUNC)) {
    Serial.print("cannot create "); Serial.println(dst); in.close(); return false;
  }
  uint64_t total = in.fileSize(), done = 0;
  uint32_t t0 = millis();
  bool ok = true;
  for (;;) {
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    else if (c == 'p') { parForce = (parForce + 1) % 4;
                         if (parForce == 1) { digitalWriteFast(PPAROUT, LOW);  Serial.println("/PPARITY FORCED LOW"); }
                         else if (parForce == 2) { digitalWriteFast(PPAROUT, HIGH); Serial.println("/PPARITY FORCED HIGH"); }
                         else if (parForce == 3) { pinMode(PPAROUT, INPUT); Serial.println("/PPARITY FLOAT (high-Z; a card pull-up should take it to 5V)"); }
                         else { pinMode(PPAROUT, OUTPUT); Serial.println("/PPARITY = computed"); }
                         if (parForce == 1 || parForce == 2) pinMode(PPAROUT, OUTPUT); }
    else if (c == 'n') { nakIgnore ^= 1;
                         Serial.println(nakIgnore ? "confirm NAK = IGNORED (pre-debug behavior)"
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  int8_t prw = digitalReadFast(PRWIN) ? 1 : 0;
  static uint8_t lastDriven = 0x00;
  if (prw != idlePRW || (prw && !idleTristate && idleDriveByte != lastDriven)) {
    if (prw && !idleTristate) { presentByte(idleDriveByte); dataPinsOutput(); lastDriven = idleDriveByte; }
    else                      { dataPinsInput(); }
    idlePRW = prw;
  }
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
